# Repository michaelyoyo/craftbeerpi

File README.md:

# CraftBeerPi

This project is shamelessly forked from https://github.com/Manuel83/craftbeerpi

This fork is intended to add support for a few new sensors and for my custom HERMS
controller PCB.

The PCB contains
-2x MAX31865 RTD Amplifiers
-1x EzoPh Amplifier
-2x Pump/Heater Outputs
-A bunch of LEDs
-Automatic control of a 12v Power Supply
-An expansion connector because I can't think of everything

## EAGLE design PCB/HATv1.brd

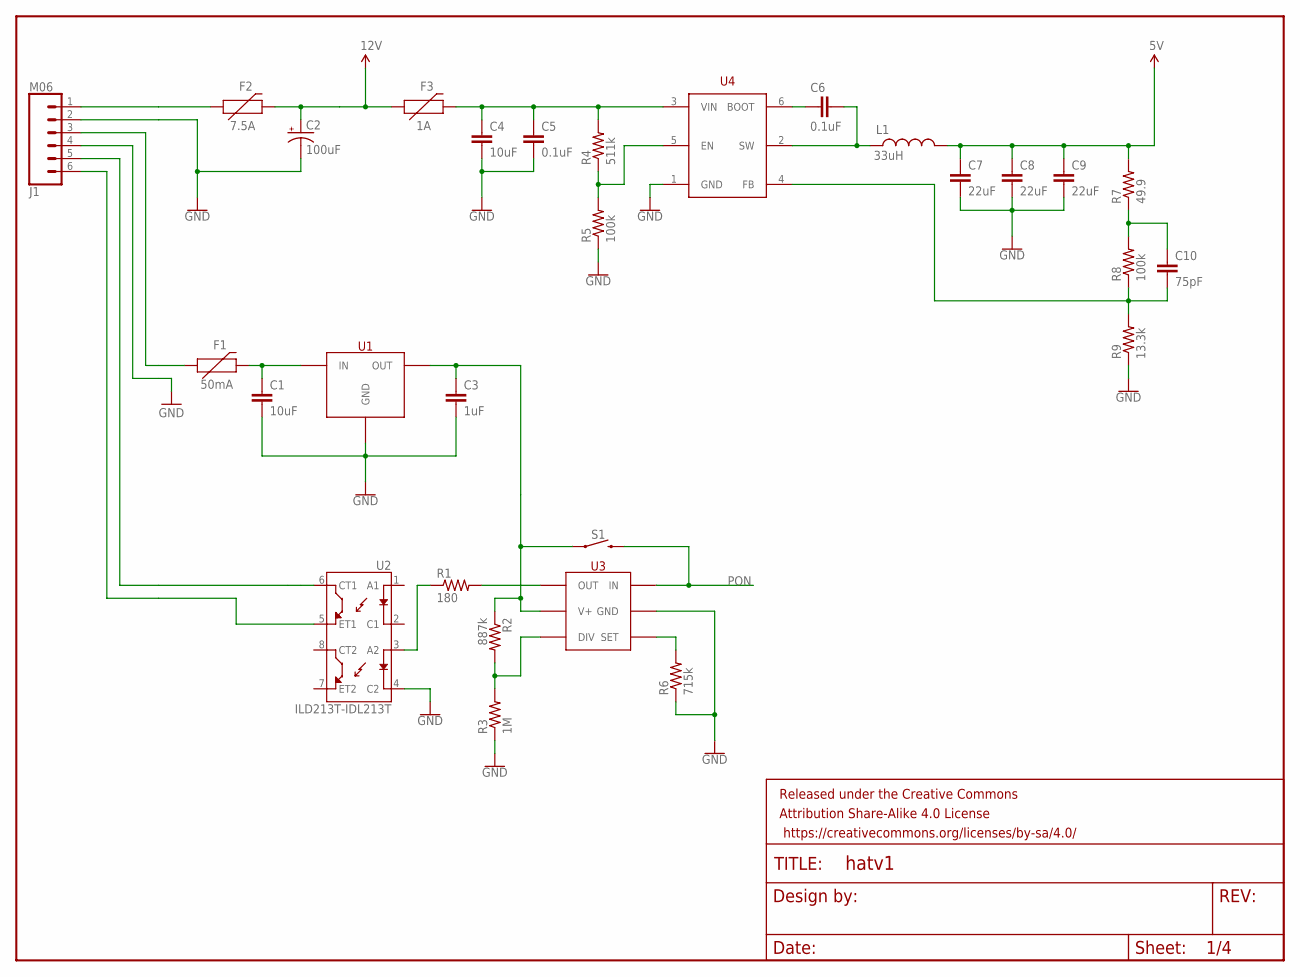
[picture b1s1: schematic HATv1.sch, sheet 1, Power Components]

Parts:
C1, C4: 10uF; 0805
C2: 100uF; PANASONIC_E
C3: 1uF; 0603-CAP
C5, C6: 0.1uF; 0603-CAP
C7, C8, C9: 22uF; 1210
C10: 75pF; 0603-CAP
F1: 50mA; PTH
F2: 7.5A; 1206
F3: 1A; 2010
FRAME1: FRAME-LETTERNO_PACKAGE; DUMMY
J1: M06; SCREWTERMINAL-3.5MM-6
L1: 33uH; SRP1265A
R1: 180; 0603-RES
R2: 887k; 0603-RES
R3: 1M; 0603-RES
R4: 511k; 0603-RES
R5, R8: 100k; 0603-RES
R6: 715k; 0603-RES
R7: 49.9; 0603-RES
R9: 13.3k; 0603-RES
S1: MOMENTARY-SWITCH-SPST-SMD-12MM; TACTILE_SWITCH_SMD_12MM
U1: NCP715; SC70
U2: ILD213T-IDL213T; SO08
U3: LT6994; SOT23-6
U4: TPS54302; SOT23-6

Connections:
5V: C7.1, C8.1, C9.1, L1.P$2 (2), R7.2; also elsewhere on the board
12V: C2.+, F2.2, F3.1; also elsewhere on the board
GND: C1.2, C2.-, C3.2, C4.2, C5.2, C7.2, C8.2, C9.2, J1.2, J1.4, R3.1, R5.1, R6.1, R9.1, U1.2 (GND), U2.4 (C2), U3.2 (GND), U4.1 (GND); also elsewhere on the board
unnamed: R1.1, U2.3 (A2)
unnamed: C6.1, U4.6 (BOOT)
unnamed: C6.2, L1.P$1 (1), U4.2 (SW)
unnamed: C10.1, R7.1, R8.2
unnamed: C10.2, R8.1, R9.2, U4.4 (FB)
unnamed: R4.1, R5.2, U4.5 (EN)
unnamed: J1.6, U2.5 (ET1)
unnamed: J1.5, U2.6 (CT1)
unnamed: R1.2, U3.6 (OUT)
unnamed: R2.2, R3.2, U3.4 (DIV)
unnamed: R6.2, U3.3 (SET)
unnamed: C3.1, R2.1, S1.1, U1.5 (OUT), U3.5 (V+)
unnamed: C1.1, F1.P$2 (2), U1.4 (IN)
unnamed: F1.P$1 (1), J1.3
unnamed: C4.1, C5.1, F3.2, R4.2, U4.3 (VIN)
unnamed: F2.1, J1.1
PON: S1.3 (2), U3.1 (IN); also elsewhere on the board

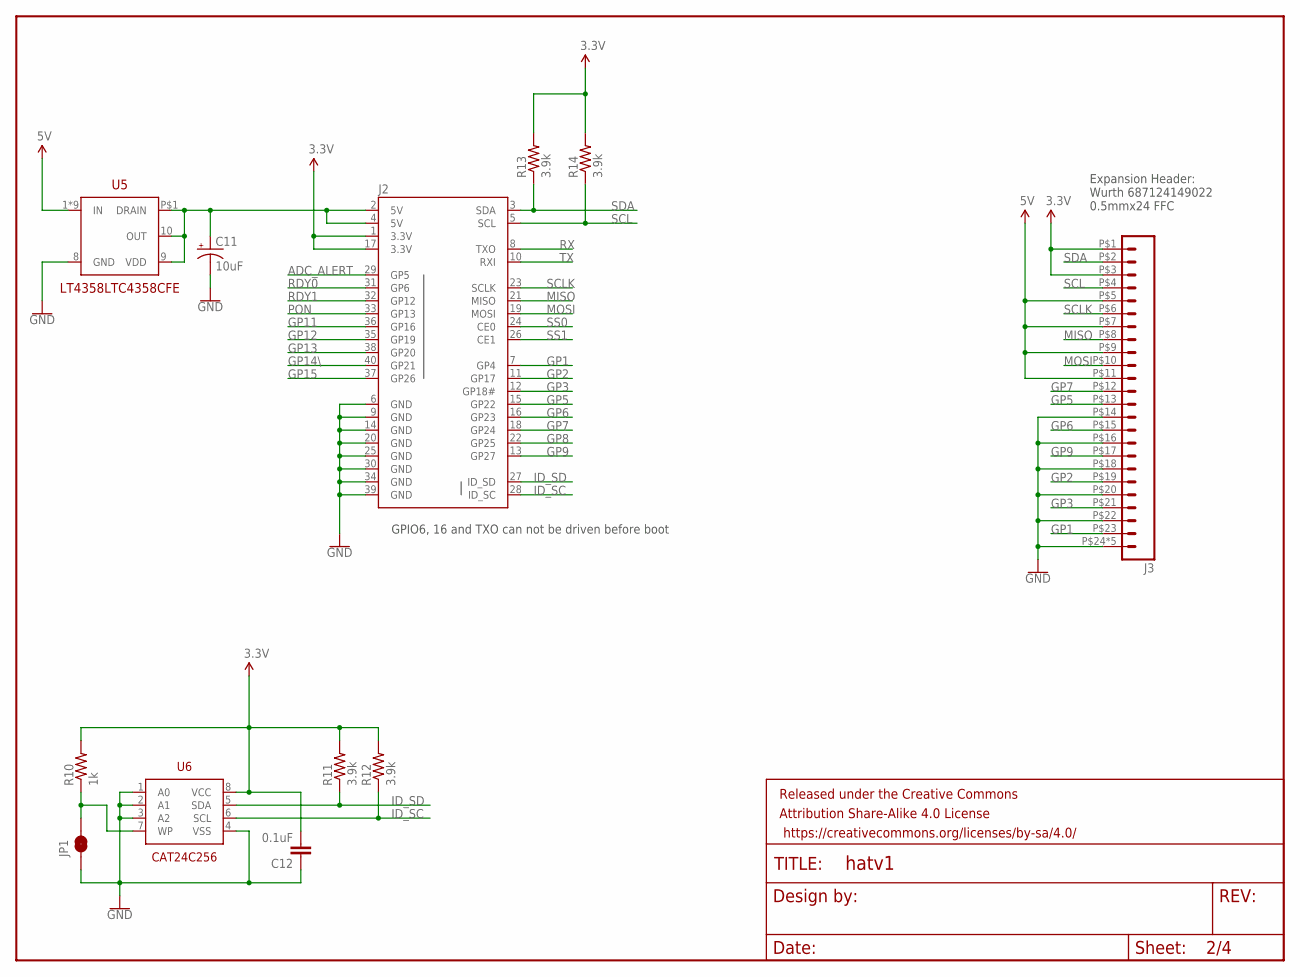
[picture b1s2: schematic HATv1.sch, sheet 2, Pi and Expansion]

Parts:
C11: 10uF; EIA3216
C12: 0.1uF; 0603-CAP
FRAME2: FRAME-LETTERNO_PACKAGE; DUMMY
J2: RASPBERRYPI-40-PIN-GPIO2X20PASSTHROUGH; 1X24SAMTEC
J3: M24FFC; FFC_24
JP1: JUMPER-PAD-2-NC_BY_TRACE; PAD-JUMPER-2-NC_BY_TRACE_YES_SILK
R10: 1k; 0603-RES
R11, R12, R13, R14: 3.9k; 0603-RES
U5: LT4358LTC4358CFE; TSSOP-16
U6: CAT24C256; SO8

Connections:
3.3V: C12.2, J2.1 (3.3V), J2.17 (3.3V), J3.P$1 (2), J3.P$3 (4), R10.2, R11.2, R12.2, R13.2, R14.2, U6.8 (VCC); also elsewhere on the board
5V: J3.P$5 (6), J3.P$7 (8), J3.P$9 (10), J3.P$11 (12), U5.1 (IN), U5.2 (IN), U5.3 (IN), U5.4 (IN), U5.12 (IN), U5.13 (IN), U5.14 (IN), U5.15 (IN), U5.16 (IN); also elsewhere on the board
ADC_ALERT: J2.29 (GP5); also elsewhere on the board
GND: C11.-, C12.1, J2.6 (GND), J2.9 (GND), J2.14 (GND), J2.20 (GND), J2.25 (GND), J2.30 (GND), J2.34 (GND), J2.39 (GND), J3.P$14 (15), J3.P$16 (17), J3.P$18 (19), J3.P$20 (21), J3.P$22 (23), J3.P$24 (25), J3.P$25 (25), J3.P$26 (25), J3.P$27 (25), J3.P$28 (25), JP1.1, U5.8 (GND), U6.1 (A0), U6.2 (A1), U6.3 (A2), U6.4 (VSS); also elsewhere on the board
GP1: J2.7 (GP4), J3.P$23 (24)
GP2: J2.11 (GP17), J3.P$19 (20)
GP3: J2.12 (GP18#), J3.P$21 (22)
GP5: J2.15 (GP22), J3.P$13 (14)
GP6: J2.16 (GP23), J3.P$15 (16)
GP7: J2.18 (GP24), J3.P$12 (13)
GP8: J2.22 (GP25)
GP9: J2.13 (GP27), J3.P$17 (18)
GP11: J2.36 (GP16)
GP12: J2.35 (GP19)
GP13: J2.38 (GP20)
GP14\: J2.40 (GP21)
GP15: J2.37 (GP26)
ID_SC: J2.28 (ID_SC), R12.1, U6.6 (SCL)
ID_SD: J2.27 (ID_SD), R11.1, U6.5 (SDA)
MISO: J2.21 (MISO), J3.P$8 (9); also elsewhere on the board
MOSI: J2.19 (MOSI), J3.P$10 (11); also elsewhere on the board
unnamed: JP1.2, R10.1, U6.7 (WP)
unnamed: C11.+, J2.2 (5V), J2.4 (5V), U5.9 (VDD), U5.10 (OUT), U5.P$1 (DRAIN)
PON: J2.33 (GP13); also elsewhere on the board
RDY0: J2.31 (GP6); also elsewhere on the board
RDY1: J2.32 (GP12); also elsewhere on the board
RX: J2.8 (TXO); also elsewhere on the board
SCL: J2.5 (SCL), J3.P$4 (5), R14.1; also elsewhere on the board
SCLK: J2.23 (SCLK), J3.P$6 (7); also elsewhere on the board
SDA: J2.3 (SDA), J3.P$2 (3), R13.1; also elsewhere on the board
SS0: J2.24 (CE0); also elsewhere on the board
SS1: J2.26 (CE1); also elsewhere on the board
TX: J2.10 (RXI); also elsewhere on the board

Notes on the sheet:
GPIO6, 16 and TXO can not be driven before boot
Expansion Header: Wurth 687124149022 0.5mmx24 FFC

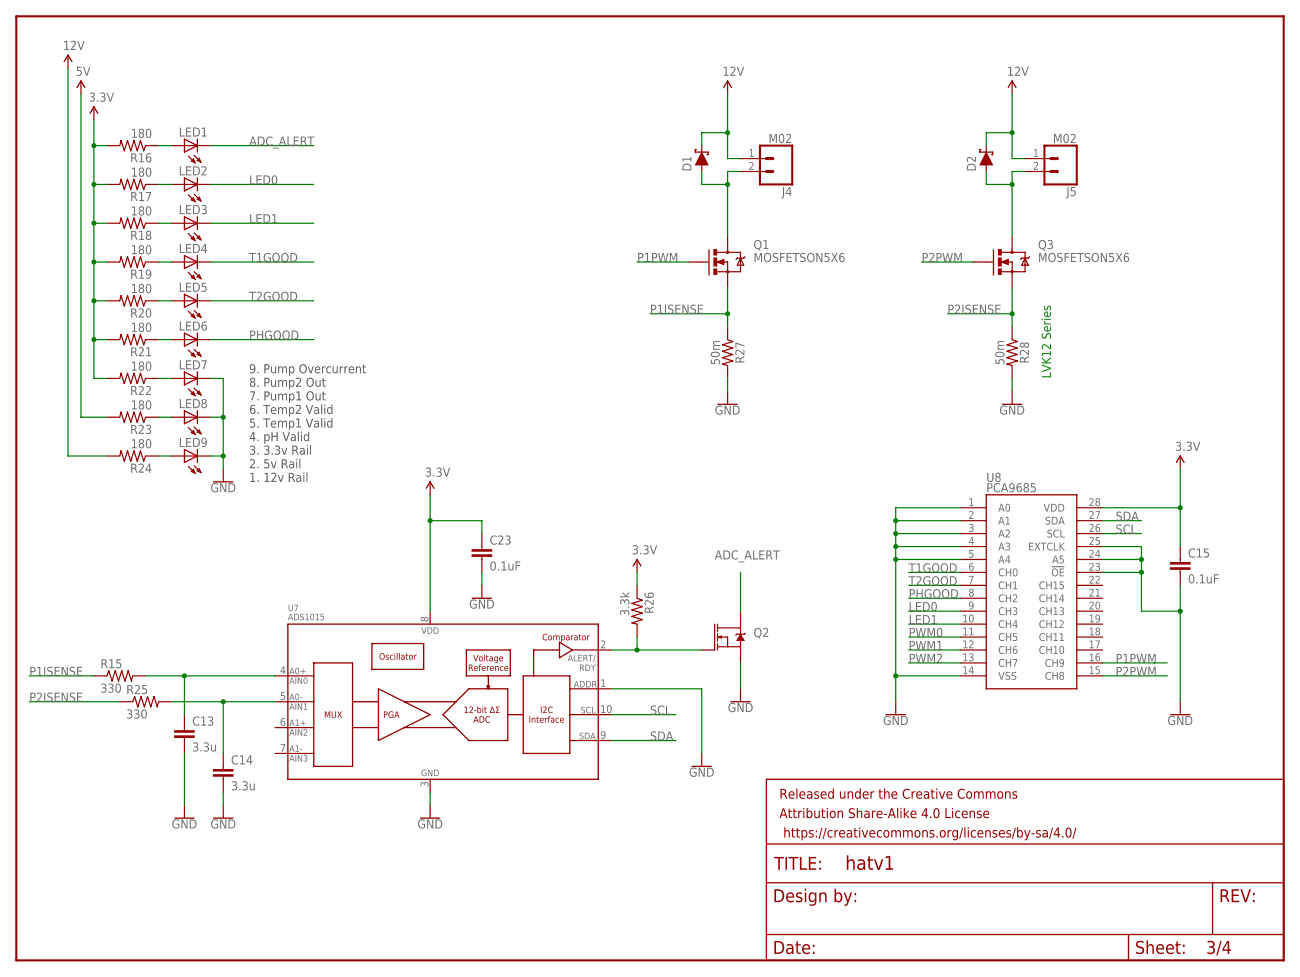
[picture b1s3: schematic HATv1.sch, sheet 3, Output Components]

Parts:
C13, C14: 3.3u; 0603
C15, C23: 0.1uF; 0603-CAP
D1, D2: DIODE-SCHOTTKY-B340A; SMA-DIODE
FRAME3: FRAME-LETTERNO_PACKAGE; DUMMY
J4, J5: M02; SCREWTERMINAL-3.5MM-2
LED1, LED2, LED3, LED4, LED5, LED6, LED7, LED8, LED9: LEDCHIP-LED0603; CHIP-LED0603
Q1, Q3: MOSFETSON5X6; SON5X6MM
Q2: MOSFET-NCH-BSS138; SOT23-3
R15, R25: 330; 0603-RES
R16, R17, R18, R19, R20, R21, R22, R23, R24: 180; 0603-RES
R26: 3.3k; 0603-RES
R27, R28: 50m; 1206
U7: ADS1015; MSOP10
U8: PCA9685; TSSOP-28_4MM

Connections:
3.3V: C15.1, C23.1, R16.2, R17.2, R18.2, R19.2, R20.2, R21.2, R22.2, R26.1, U7.8 (VDD), U8.28 (VDD); also elsewhere on the board
5V: R23.2; also elsewhere on the board
12V: D1.C, D2.C, J4.1, J5.1, R24.2; also elsewhere on the board
ADC_ALERT: LED1.C, Q2.3 (D); also elsewhere on the board
GND: C13.2, C14.2, C15.2, C23.2, LED7.C, LED8.C, LED9.C, Q2.2 (S), R27.2, R28.2, U7.1 (ADDR), U7.3 (VSS), U8.1 (A0), U8.2 (A1), U8.3 (A2), U8.4 (A3), U8.5 (A4), U8.14 (VSS), U8.23 (!OE), U8.24 (A5), U8.25 (EXTCLK); also elsewhere on the board
LED0: LED2.C, U8.9 (CH3)
LED1: LED3.C, U8.10 (CH4)
unnamed: LED1.A, R16.1
unnamed: D1.A, J4.2, Q1.P$5 (D), Q1.P$6 (D), Q1.P$7 (D), Q1.P$8 (D), Q1.P$9 (D)
unnamed: D2.A, J5.2, Q3.P$5 (D), Q3.P$6 (D), Q3.P$7 (D), Q3.P$8 (D), Q3.P$9 (D)
unnamed: C13.1, R15.2, U7.4 (AIN0)
unnamed: Q2.1 (G), R26.2, U7.2 (ALERT/RDY)
unnamed: LED2.A, R17.1
unnamed: LED3.A, R18.1
unnamed: LED4.A, R19.1
unnamed: LED5.A, R20.1
unnamed: LED6.A, R21.1
unnamed: LED7.A, R22.1
unnamed: LED8.A, R23.1
unnamed: LED9.A, R24.1
unnamed: C14.1, R25.2, U7.5 (AIN1)
P1ISENSE: Q1.P$1 (S), Q1.P$2 (S), Q1.P$3 (S), R15.1, R27.1
P1PWM: Q1.P$4 (G), U8.16 (CH9)
P2ISENSE: Q3.P$1 (S), Q3.P$2 (S), Q3.P$3 (S), R25.1, R28.1
P2PWM: Q3.P$4 (G), U8.15 (CH8)
PHGOOD: LED6.C, U8.8 (CH2)
PWM0: U8.11 (CH5)
PWM1: U8.12 (CH6)
PWM2: U8.13 (CH7)
SCL: U7.10 (SCL), U8.26 (SCL); also elsewhere on the board
SDA: U7.9 (SDA), U8.27 (SDA); also elsewhere on the board
T1GOOD: LED4.C, U8.6 (CH0)
T2GOOD: LED5.C, U8.7 (CH1)

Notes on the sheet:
9. Pump Overcurrent 8. Pump2 Out 7. Pump1 Out 6. Temp2 Valid 5. Temp1 Valid 4. pH Valid 3. 3.3v Rail 2. 5v Rail 1. 12v Rail
LVK12 Series

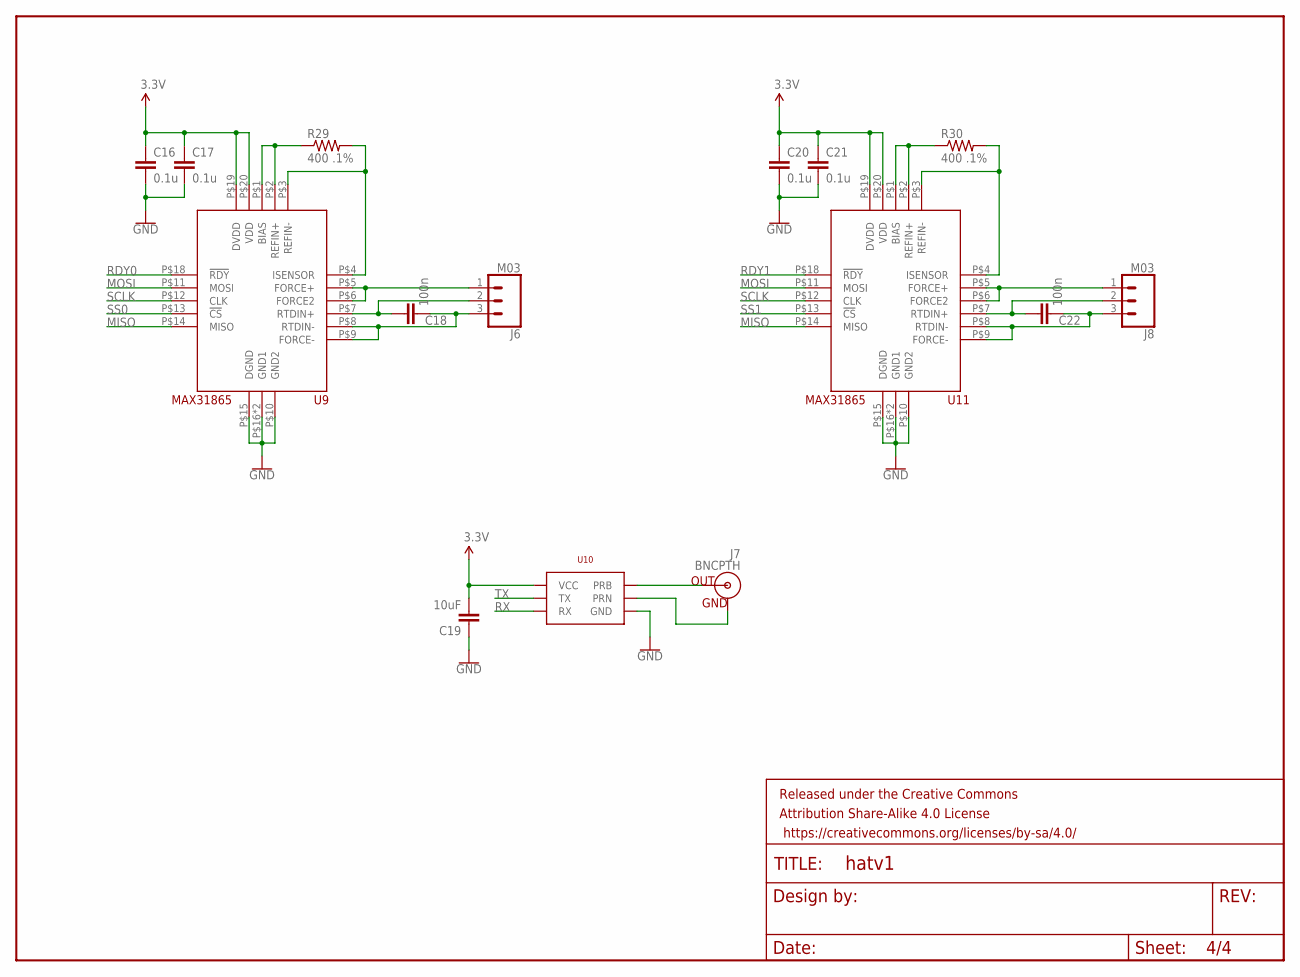
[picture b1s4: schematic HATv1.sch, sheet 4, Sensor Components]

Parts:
C16, C17, C20, C21: 0.1u; 0603-CAP
C18, C22: 100n; 0603-CAP
C19: 10uF; 1206
FRAME4: FRAME-LETTERNO_PACKAGE; DUMMY
J6, J8: M03; 1X03
J7: BNCPTH; BNC
R29, R30: 400 .1%; 0603-RES
U9, U11: MAX31865; TQFN20
U10: EZOPH

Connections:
3.3V: C16.1, C17.1, C19.2, C20.1, C21.1, U9.P$19 (DVDD), U9.P$20 (VDD), U10.VCC, U11.P$19 (DVDD), U11.P$20 (VDD); also elsewhere on the board
GND: C16.2, C17.2, C19.1, C20.2, C21.2, U9.P$10 (GND2), U9.P$15 (DGND), U9.P$16 (GND1), U9.P$21 (GND1), U10.GND, U11.P$10 (GND2), U11.P$15 (DGND), U11.P$16 (GND1), U11.P$21 (GND1); also elsewhere on the board
MISO: U9.P$14 (MISO), U11.P$14 (MISO); also elsewhere on the board
MOE2: J6.1, U9.P$5 (FORCE+), U9.P$6 (FORCE2)
MOE3: J8.1, U11.P$5 (FORCE+), U11.P$6 (FORCE2)
MOSI: U9.P$11 (MOSI), U11.P$11 (MOSI); also elsewhere on the board
unnamed: J7.S (OUT), U10.PRB
unnamed: J7.GND, U10.PGND (PRN)
unnamed: R29.1, U9.P$1 (BIAS), U9.P$2 (REFIN+)
unnamed: R29.2, U9.P$3 (REFIN-), U9.P$4 (ISENSOR)
unnamed: C18.2, J6.3, U9.P$8 (RTDIN-), U9.P$9 (FORCE-)
unnamed: C18.1, J6.2, U9.P$7 (RTDIN+)
unnamed: R30.1, U11.P$1 (BIAS), U11.P$2 (REFIN+)
unnamed: R30.2, U11.P$3 (REFIN-), U11.P$4 (ISENSOR)
unnamed: C22.2, J8.3, U11.P$8 (RTDIN-), U11.P$9 (FORCE-)
unnamed: C22.1, J8.2, U11.P$7 (RTDIN+)
RDY0: U9.P$18 (!RDY); also elsewhere on the board
RDY1: U11.P$18 (!RDY); also elsewhere on the board
RX: U10.RX; also elsewhere on the board
SCLK: U9.P$12 (CLK), U11.P$12 (CLK); also elsewhere on the board
SS0: U9.P$13 (!CS); also elsewhere on the board
SS1: U11.P$13 (!CS); also elsewhere on the board
TX: U10.TX; also elsewhere on the board

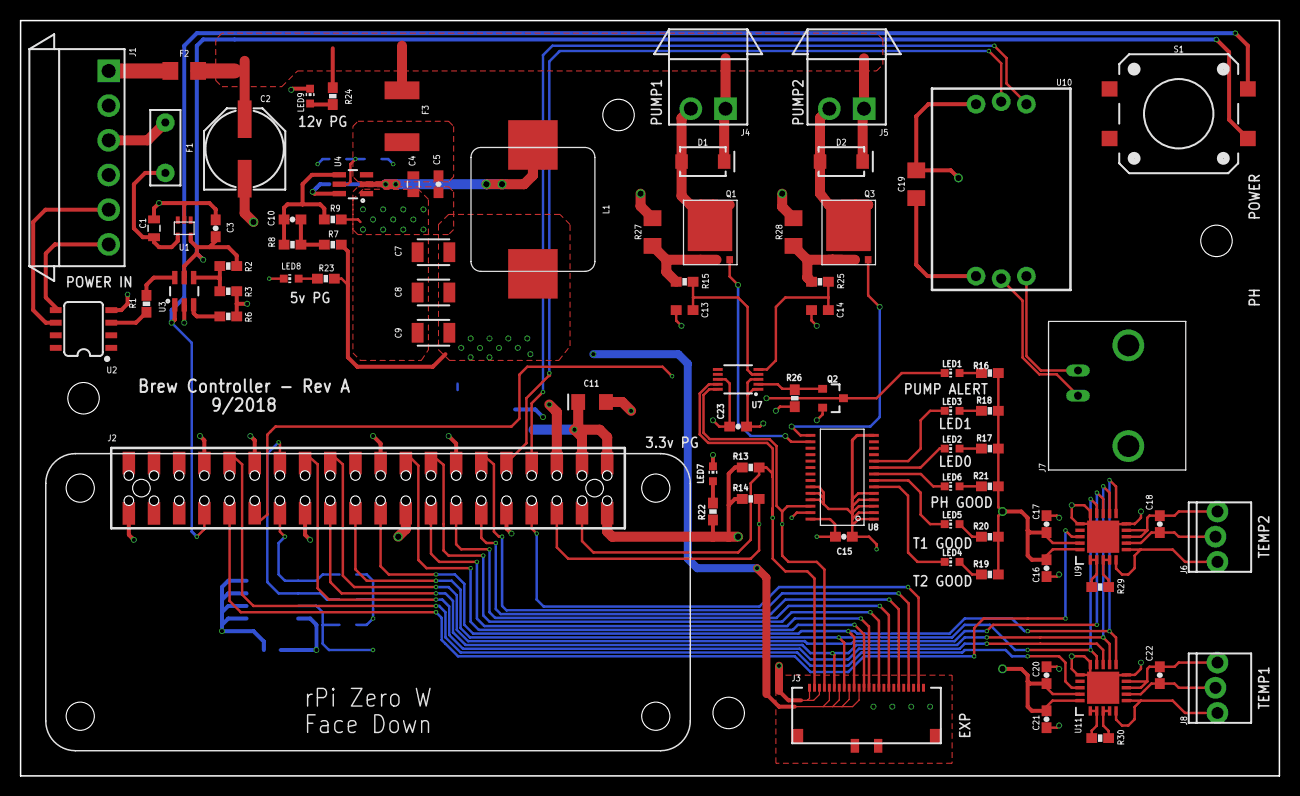
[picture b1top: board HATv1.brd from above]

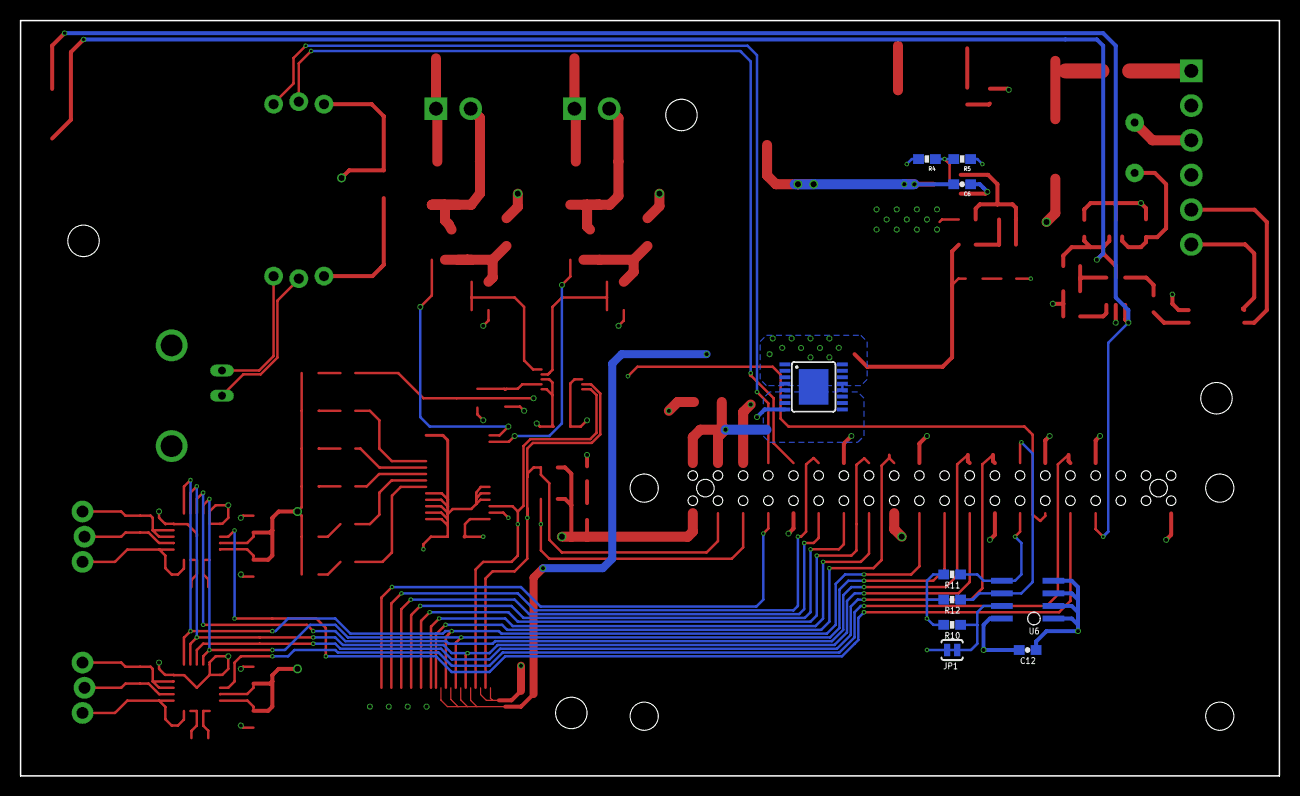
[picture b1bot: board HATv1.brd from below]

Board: 4 copper layers, 127.0 x 76.2 mm, 96 parts (10 on the bottom side), 79 nets.

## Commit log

2018-10-27 Added PCB
2018-10-28 Added MAX31865
    *hopefully added. not sure where else it's gonna show up...

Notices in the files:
parts and their libraries:
SparkFun-Passives: Licensing: Creative Commons ShareAlike 4.0 International - https://creativecommons.org/licenses/by-sa/4.0
SparkFun-Aesthetics: Released under the Creative Commons Attribution Share-Alike 4.0 License
SparkFun-Aesthetics: https://creativecommons.org/licenses/by-sa/4.0
